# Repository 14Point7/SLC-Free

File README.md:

SLC-Free
========

SLC Free is the only open source Wideband O2 Controller that works and is worth a damn

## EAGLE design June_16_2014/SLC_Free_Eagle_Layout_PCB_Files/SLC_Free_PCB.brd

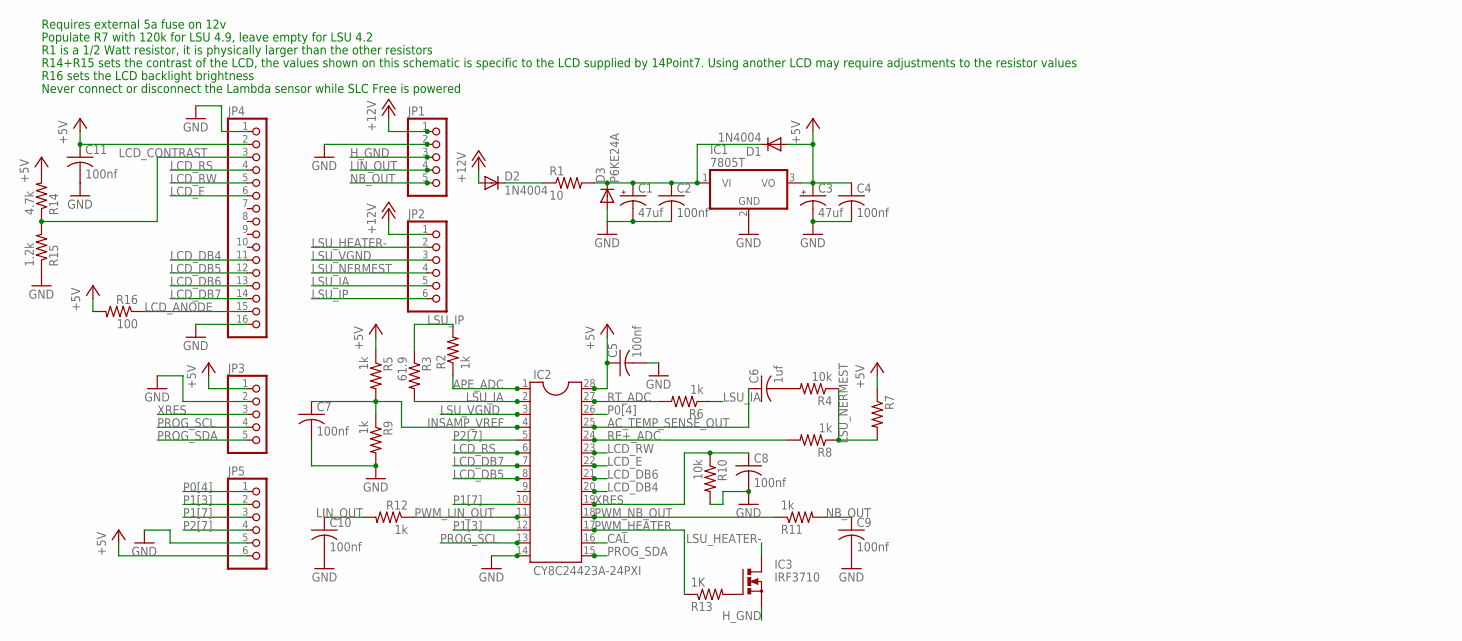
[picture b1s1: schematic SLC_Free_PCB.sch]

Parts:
C1, C3: 47uf; E2-5
C2, C4, C5, C7, C8, C9, C10, C11: 100nf; C025-025X050
C6: 1uf; C025-025X050
D1, D2: 1N4004; DO41-10
D3: P6KE24A; DO41-10
IC1: 7805T; TO220H
IC2: CY8C24423A-24PXI; DIL28-3
IC3: IRF3710; TO220BH
JP1, JP3: PINHD-1X5; 1X05
JP2, JP5: PINHD-1X6; 1X06
JP4: PINHD-1X16; 1X16
R1: 10; 0309/12
R2, R5, R6, R8, R9, R11, R12: 1k; 0204/7
R3: 61.9; 0204/7
R4, R10: 10k; 0204/7
R7: R-US_0204/7; 0204/7
R13: 1K; 0204/7
R14: 4.7k; 0204/7
R15: 1.2k; 0204/7
R16: 100; 0204/7

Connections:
+5V: C3.+, C4.1, C5.1, C11.1, D1.A, IC1.3 (VO), IC2.28, JP3.1, JP4.2, JP5.6, R5.1, R7.1, R14.2, R16.2
+12V: D2.A, JP1.1, JP2.1
AC_TEMP_SENSE_OUT: C6.1, IC2.25
APE_ADC: IC2.1, R2.1
CAL: IC2.16
GND: C1.-, C2.2, C3.-, C4.2, C5.2, C7.2, C8.2, C9.2, C10.2, C11.2, D3.A, IC1.2 (GND), IC2.14, JP1.2, JP3.2, JP4.1, JP4.16, JP5.5, R9.2, R10.2, R15.1
H_GND: IC3.S, JP1.3
INSAMP_VREF: C7.1, IC2.4, R5.2, R9.1
LCD_ANODE: JP4.15, R16.1
LCD_CONTRAST: JP4.3, R14.1, R15.2
LCD_DB4: IC2.20, JP4.11
LCD_DB5: IC2.8, JP4.12
LCD_DB6: IC2.21, JP4.13
LCD_DB7: IC2.7, JP4.14
LCD_E: IC2.22, JP4.6
LCD_RS: IC2.6, JP4.4
LCD_RW: IC2.23, JP4.5
LIN_OUT: C10.1, JP1.4, R12.2
LSU_HEATER-: IC3.D, JP2.2
LSU_IA: IC2.2, JP2.5, R3.2, R6.1
LSU_IP: JP2.6, R2.2, R3.1
LSU_NERMEST: JP2.4, R4.1, R7.2, R8.1
LSU_VGND: IC2.3, JP2.3
unnamed: C6.2, R4.2
unnamed: C1.+, C2.1, D1.C, D3.C, IC1.1 (VI), R1.2
unnamed: IC3.G, R13.2
unnamed: D2.C, R1.1
NB_OUT: C9.1, JP1.5, R11.2
P0[4]: IC2.26, JP5.1
P1[3]: IC2.12, JP5.2
P1[7]: IC2.10, JP5.3
P2[7]: IC2.5, JP5.4
PROG_SCL: IC2.13, JP3.4
PROG_SDA: IC2.15, JP3.5
PWM_HEATER: IC2.17, R13.1
PWM_LIN_OUT: IC2.11, R12.1
PWM_NB_OUT: IC2.18, R11.1
RE+_ADC: IC2.24, R8.2
RT_ADC: IC2.27, R6.2
XRES: C8.1, IC2.19, JP3.3, R10.1

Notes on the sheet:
Requires external 5a fuse on 12v
Populate R7 with 120k for LSU 4.9, leave empty for LSU 4.2
R16 sets the LCD backlight brightness
R1 is a 1/2 Watt resistor, it is physically larger than the other resistors
R14+R15 sets the contrast of the LCD, the values shown on this schematic is specific to the LCD supplied by 14Point7. Using another LCD may require adjustments to the resistor values
Never connect or disconnect the Lambda sensor while SLC Free is powered

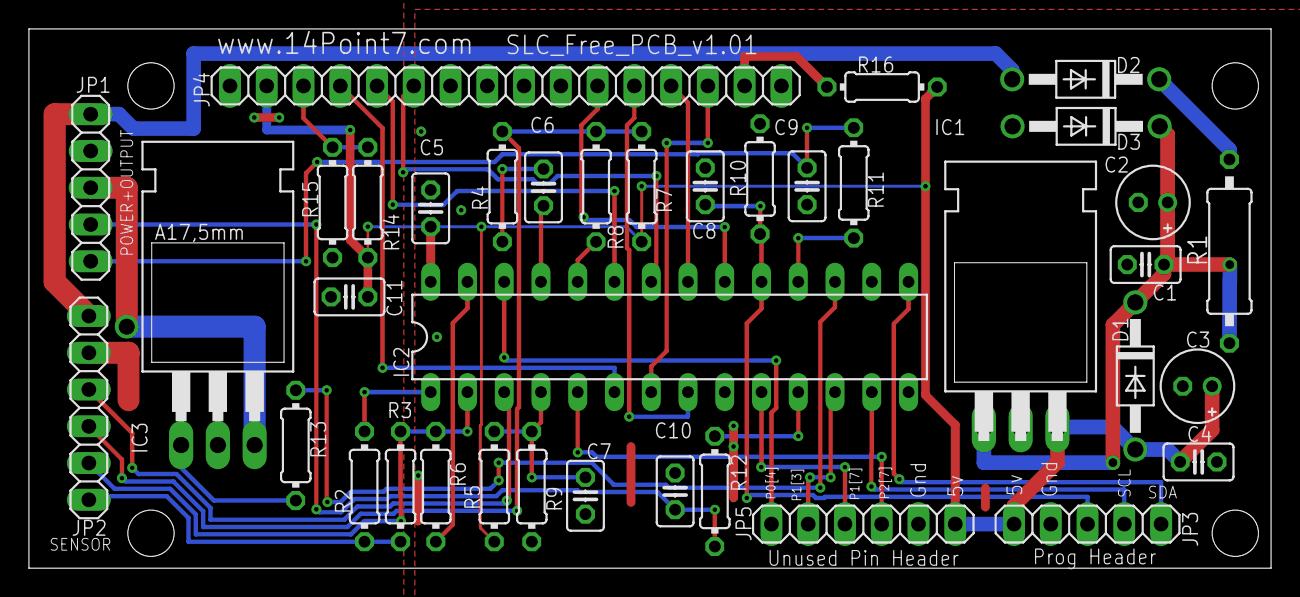
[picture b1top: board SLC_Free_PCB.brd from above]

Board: 2 copper layers, 85.8 x 37.3 mm, 38 parts (0 on the bottom side), 39 nets.

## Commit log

2013-12-19 Added SLC_Free_Manual
2019-08-21 New PCB & Firmware: Lambda and temp is displayed as text
